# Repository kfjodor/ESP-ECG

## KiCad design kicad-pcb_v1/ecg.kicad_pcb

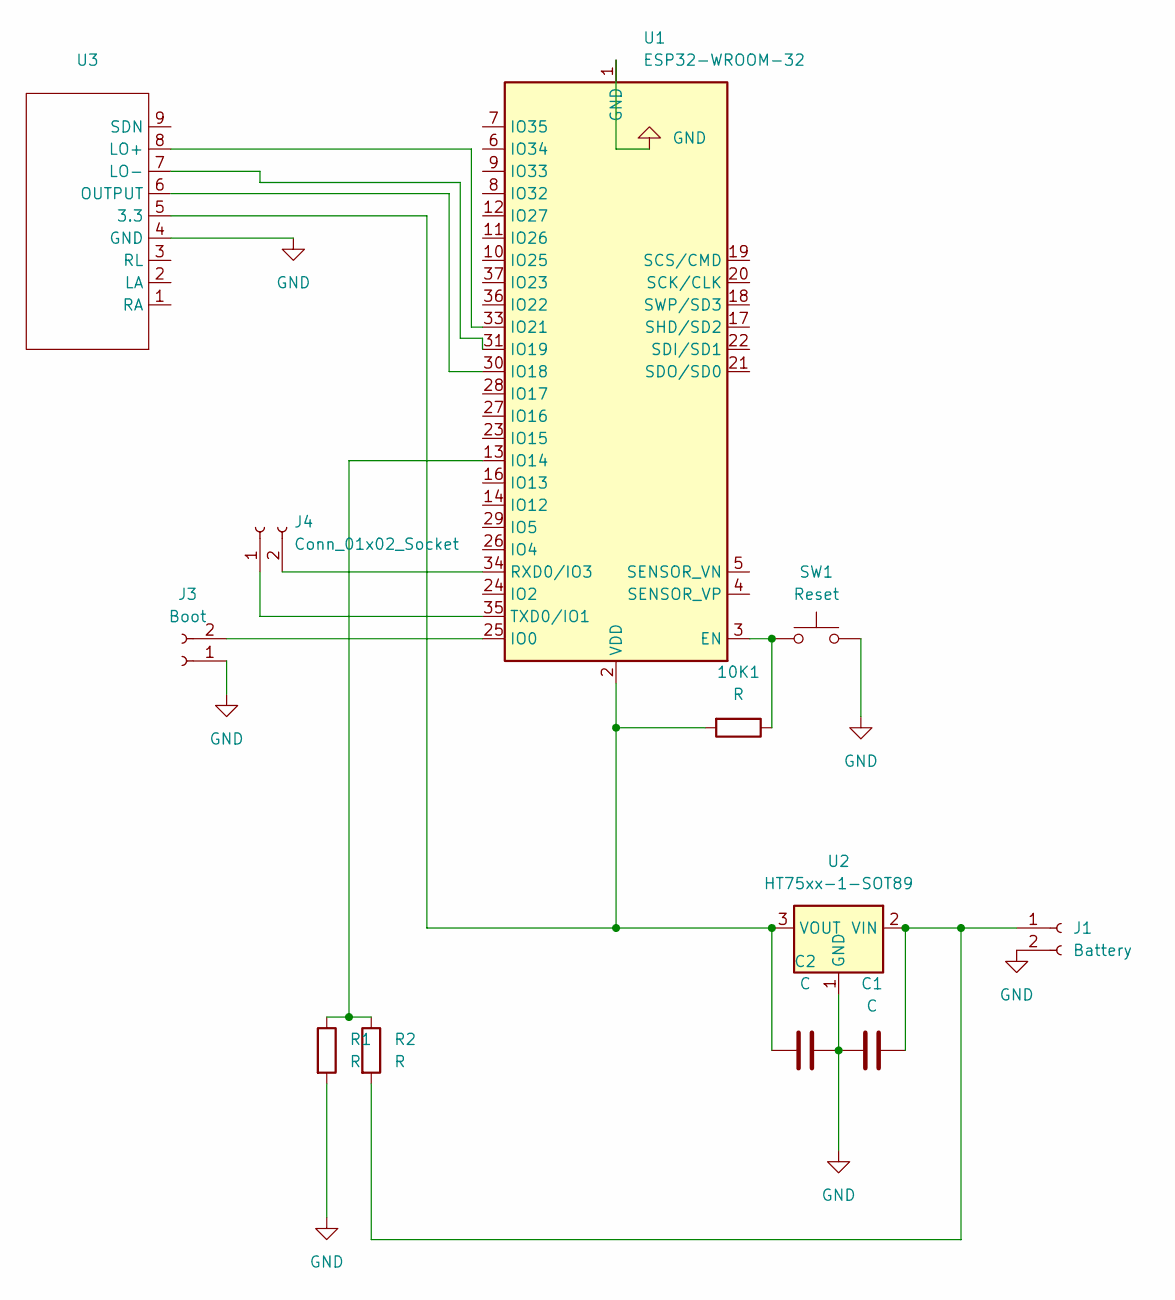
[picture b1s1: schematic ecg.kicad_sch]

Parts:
10K1: R; R_0603_1608Metric_Pad0.98x0.95mm_HandSolder
C1, C2: C; CP_Radial_D5.0mm_P2.50mm
J1: Battery; PinSocket_1x02_P2.54mm_Vertical
J3: Boot; PinHeader_1x02_P2.54mm_Vertical
J4: Conn_01x02_Socket; C_0603_1608Metric_Pad1.08x0.95mm_HandSolder
R1, R2: R; R_0603_1608Metric_Pad0.98x0.95mm_HandSolder
SW1: Reset; SW_DIP_SPSTx01_Slide_6.7x4.1mm_W8.61mm_P2.54mm_LowProfile
U1: ESP32-WROOM-32
U2: HT75xx-1-SOT89; SOT-89-3
U3: ad8232_board

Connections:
GND: C1.2, C2.2, J1.2, J3.1, R1.2, SW1.2, U1.1 (GND), U1.15 (GND), U1.38 (GND), U1.39 (GND), U2.1 (GND), U3.4 (GND)
unnamed: C1.1, J1.1, R2.2, U2.2 (VIN)
unnamed: J3.2, U1.25 (IO0)
unnamed: J4.1, U1.35 (TXD0/IO1)
unnamed: J4.2, U1.34 (RXD0/IO3)
unnamed: 10K1.1, SW1.1, U1.3 (EN)
unnamed: R1.1, R2.1, U1.13 (IO14)
unnamed: U1.30 (IO18), U3.6 (OUTPUT)
unnamed: U1.31 (IO19), U3.7 (LO-)
unnamed: U1.33 (IO21), U3.8 (LO+)
unnamed: 10K1.2, C2.1, U1.2 (VDD), U2.3 (VOUT), U3.5 (3.3)

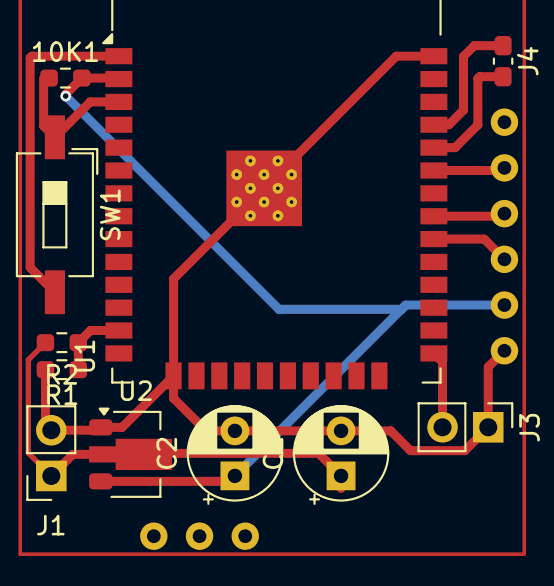
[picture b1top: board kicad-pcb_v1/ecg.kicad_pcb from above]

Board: 2 copper layers, 12 parts (0 on the bottom side), 11 nets.

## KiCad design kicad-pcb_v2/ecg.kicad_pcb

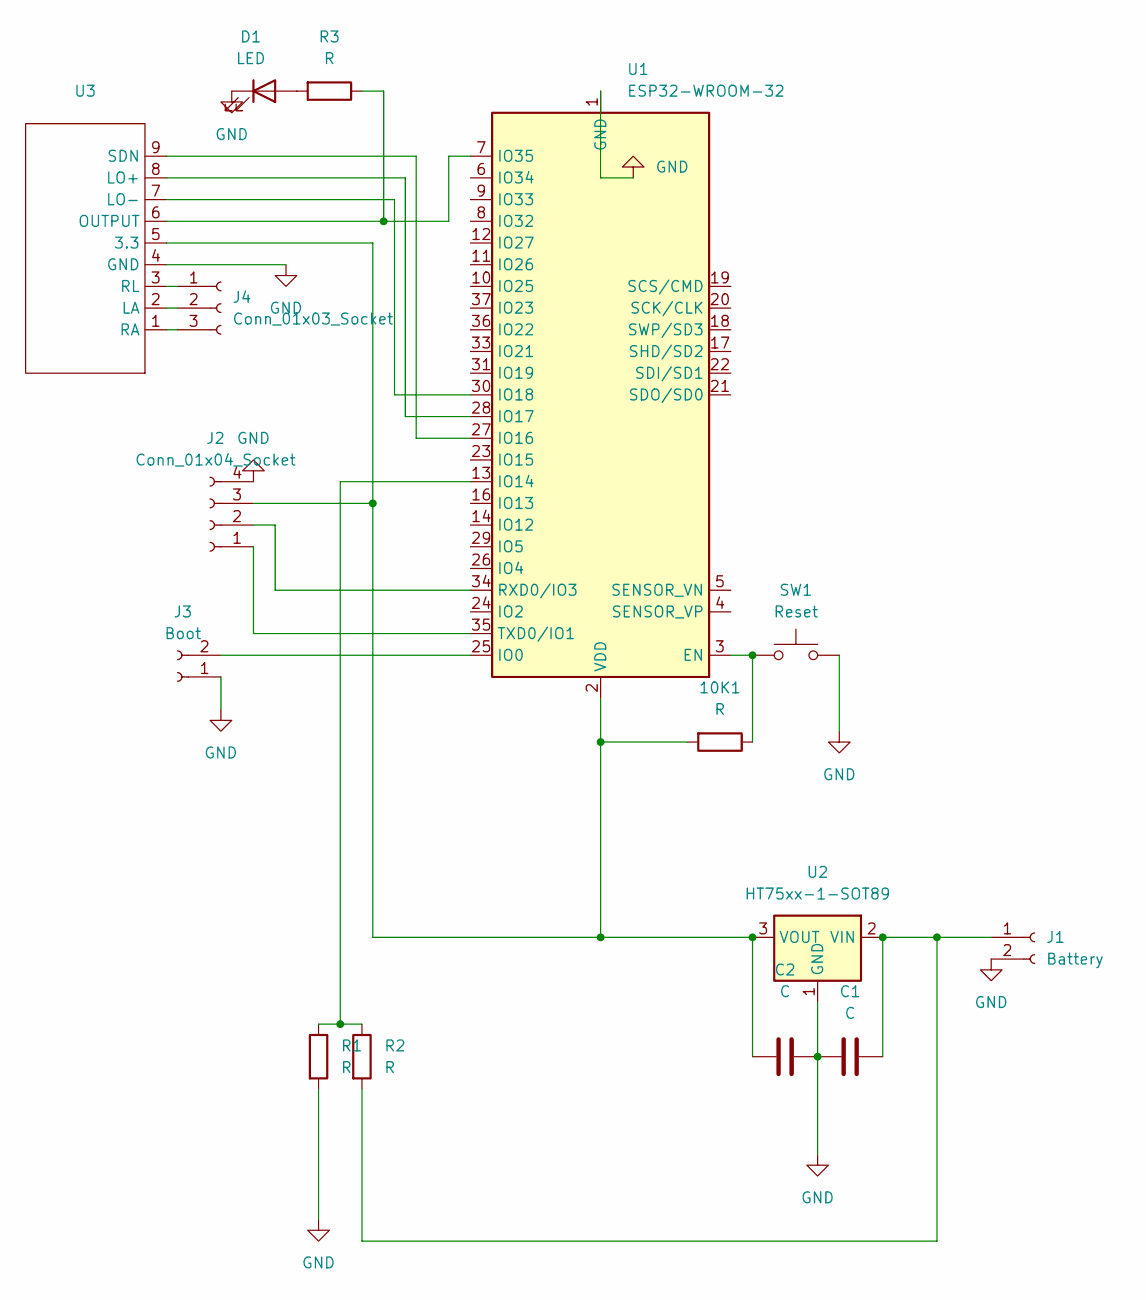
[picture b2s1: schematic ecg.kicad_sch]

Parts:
10K1: R; R_1206_3216Metric_Pad1.30x1.75mm_HandSolder
C1, C2: C; CP_Radial_D5.0mm_P2.50mm
D1: LED; LED_D5.0mm
J1: Battery; PinSocket_1x02_P2.54mm_Vertical
J2: Conn_01x04_Socket; PinHeader_1x04_P2.54mm_Vertical
J3: Boot; PinHeader_1x02_P2.54mm_Vertical
J4: Conn_01x03_Socket; PinHeader_1x03_P2.54mm_Vertical
R1, R2: R; R_1206_3216Metric_Pad1.30x1.75mm_HandSolder
R3: R; R_Axial_DIN0207_L6.3mm_D2.5mm_P10.16mm_Horizontal
SW1: Reset; SW_DIP_SPSTx01_Slide_6.7x4.1mm_W8.61mm_P2.54mm_LowProfile
U1: ESP32-WROOM-32
U2: HT75xx-1-SOT89; SOT-89-3
U3: ad8232_board

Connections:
GND: C1.2, C2.2, D1.1 (K), J1.2, J2.4, J3.1, R1.2, SW1.2, U1.1 (GND), U1.15 (GND), U1.38 (GND), U1.39 (GND), U2.1 (GND), U3.4 (GND)
unnamed: D1.2 (A), R3.2
unnamed: C1.1, J1.1, R2.2, U2.2 (VIN)
unnamed: J2.1, U1.35 (TXD0/IO1)
unnamed: J2.2, U1.34 (RXD0/IO3)
unnamed: 10K1.2, C2.1, J2.3, U1.2 (VDD), U2.3 (VOUT), U3.5 (3.3)
unnamed: J3.2, U1.25 (IO0)
unnamed: J4.1, U3.3 (RL)
unnamed: J4.2, U3.2 (LA)
unnamed: J4.3, U3.1 (RA)
unnamed: 10K1.1, SW1.1, U1.3 (EN)
unnamed: R1.1, R2.1, U1.13 (IO14)
unnamed: U1.27 (IO16), U3.9 (SDN)
unnamed: U1.28 (IO17), U3.8 (LO+)
unnamed: U1.30 (IO18), U3.7 (LO-)
unnamed: R3.1, U1.7 (IO35), U3.6 (OUTPUT)

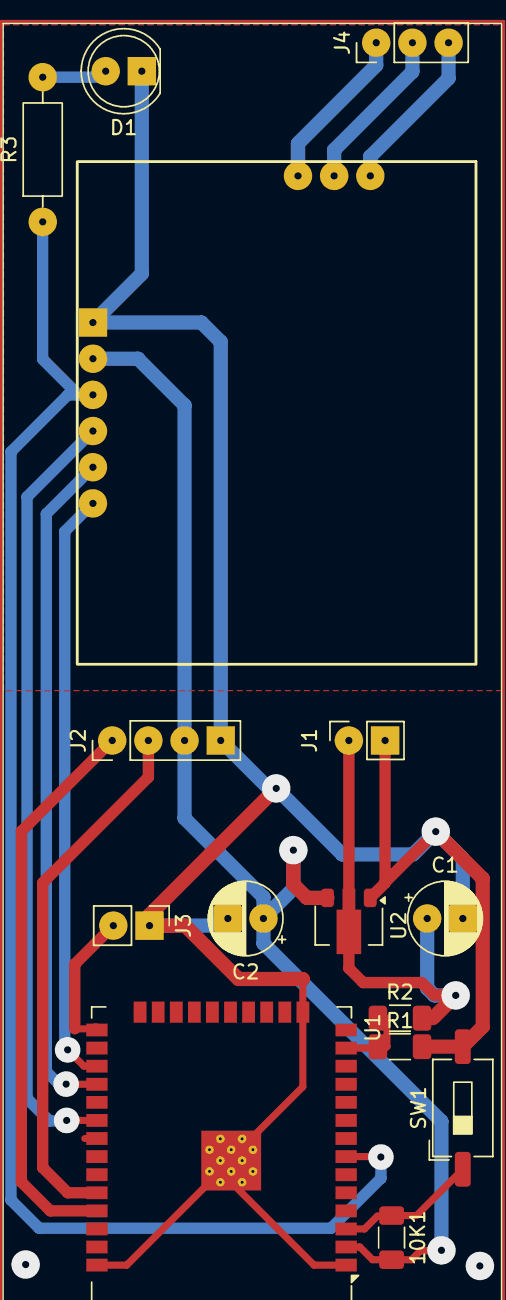
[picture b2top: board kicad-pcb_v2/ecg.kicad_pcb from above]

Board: 2 copper layers, 15 parts (0 on the bottom side), 16 nets.

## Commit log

2025-11-19 finished pcb_v2
2026-02-08 add POC android app
2026-02-09 remove stop button, make pause-resume
